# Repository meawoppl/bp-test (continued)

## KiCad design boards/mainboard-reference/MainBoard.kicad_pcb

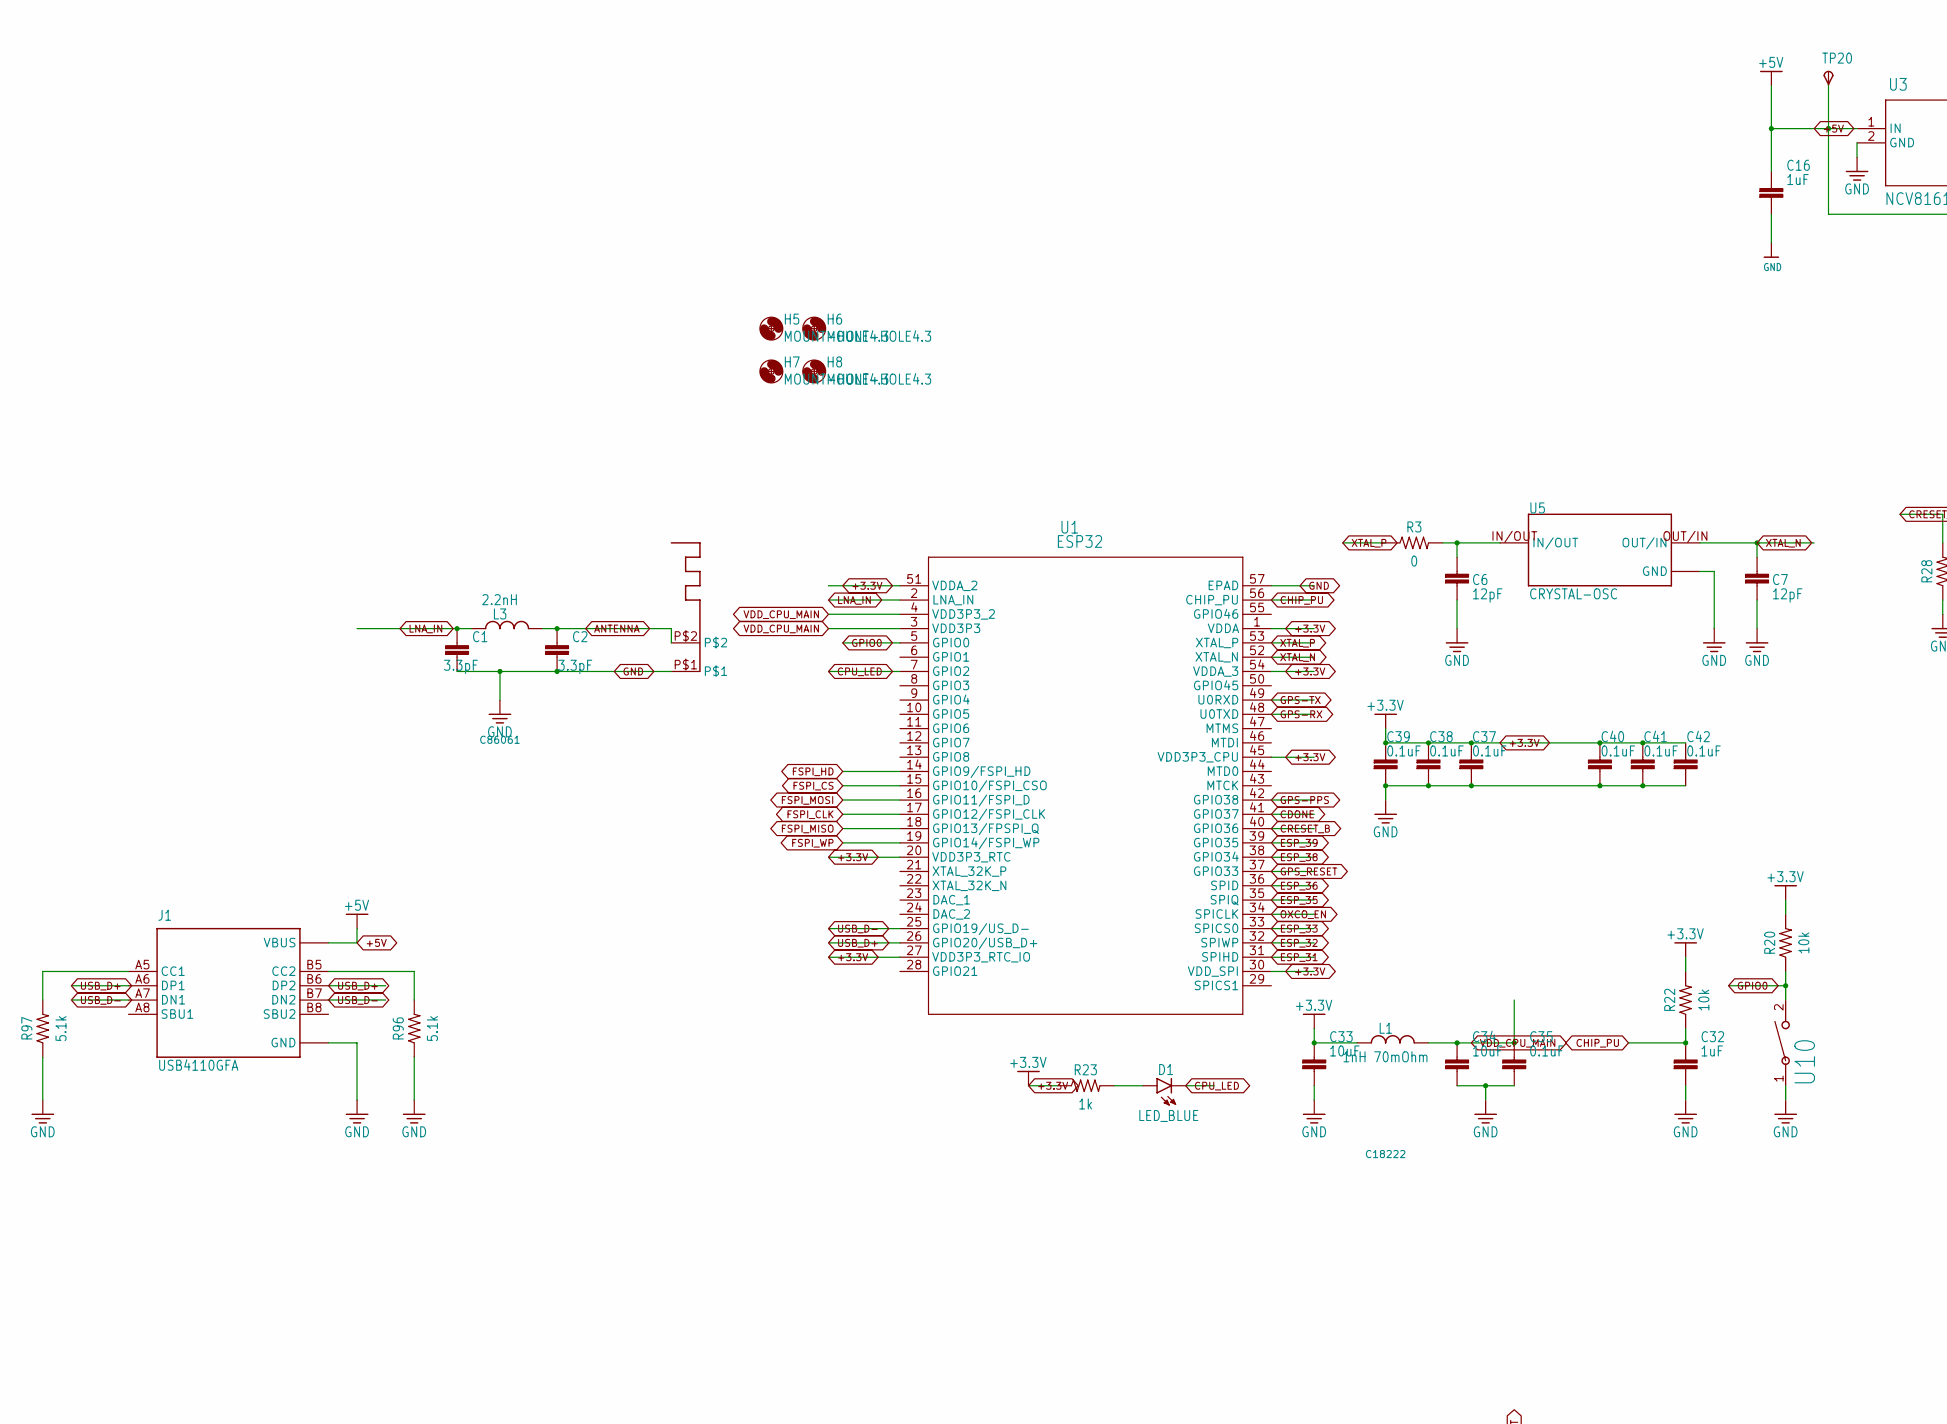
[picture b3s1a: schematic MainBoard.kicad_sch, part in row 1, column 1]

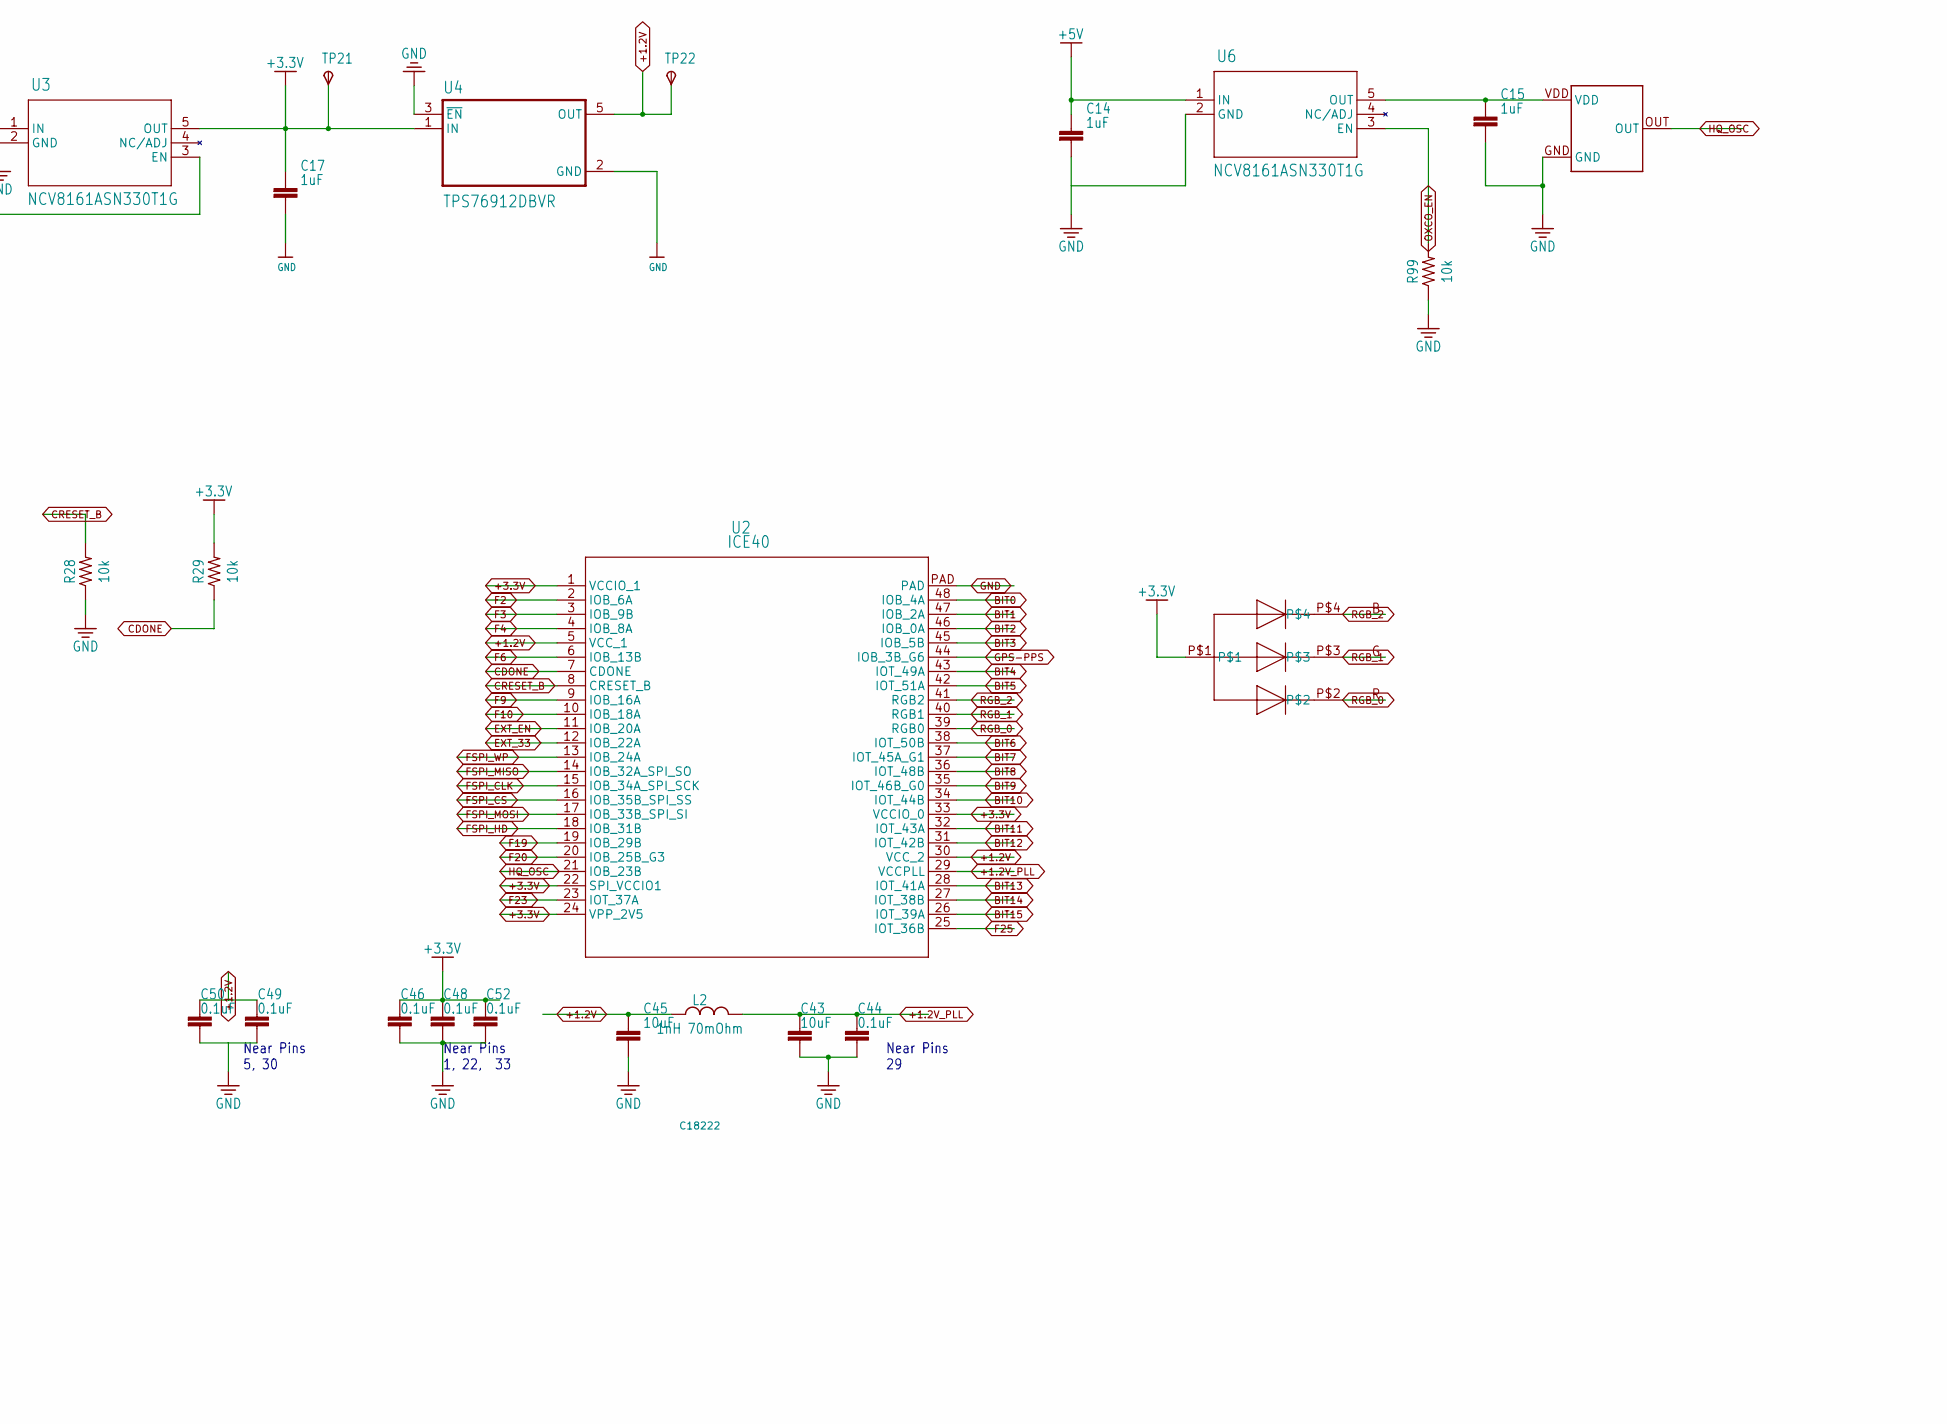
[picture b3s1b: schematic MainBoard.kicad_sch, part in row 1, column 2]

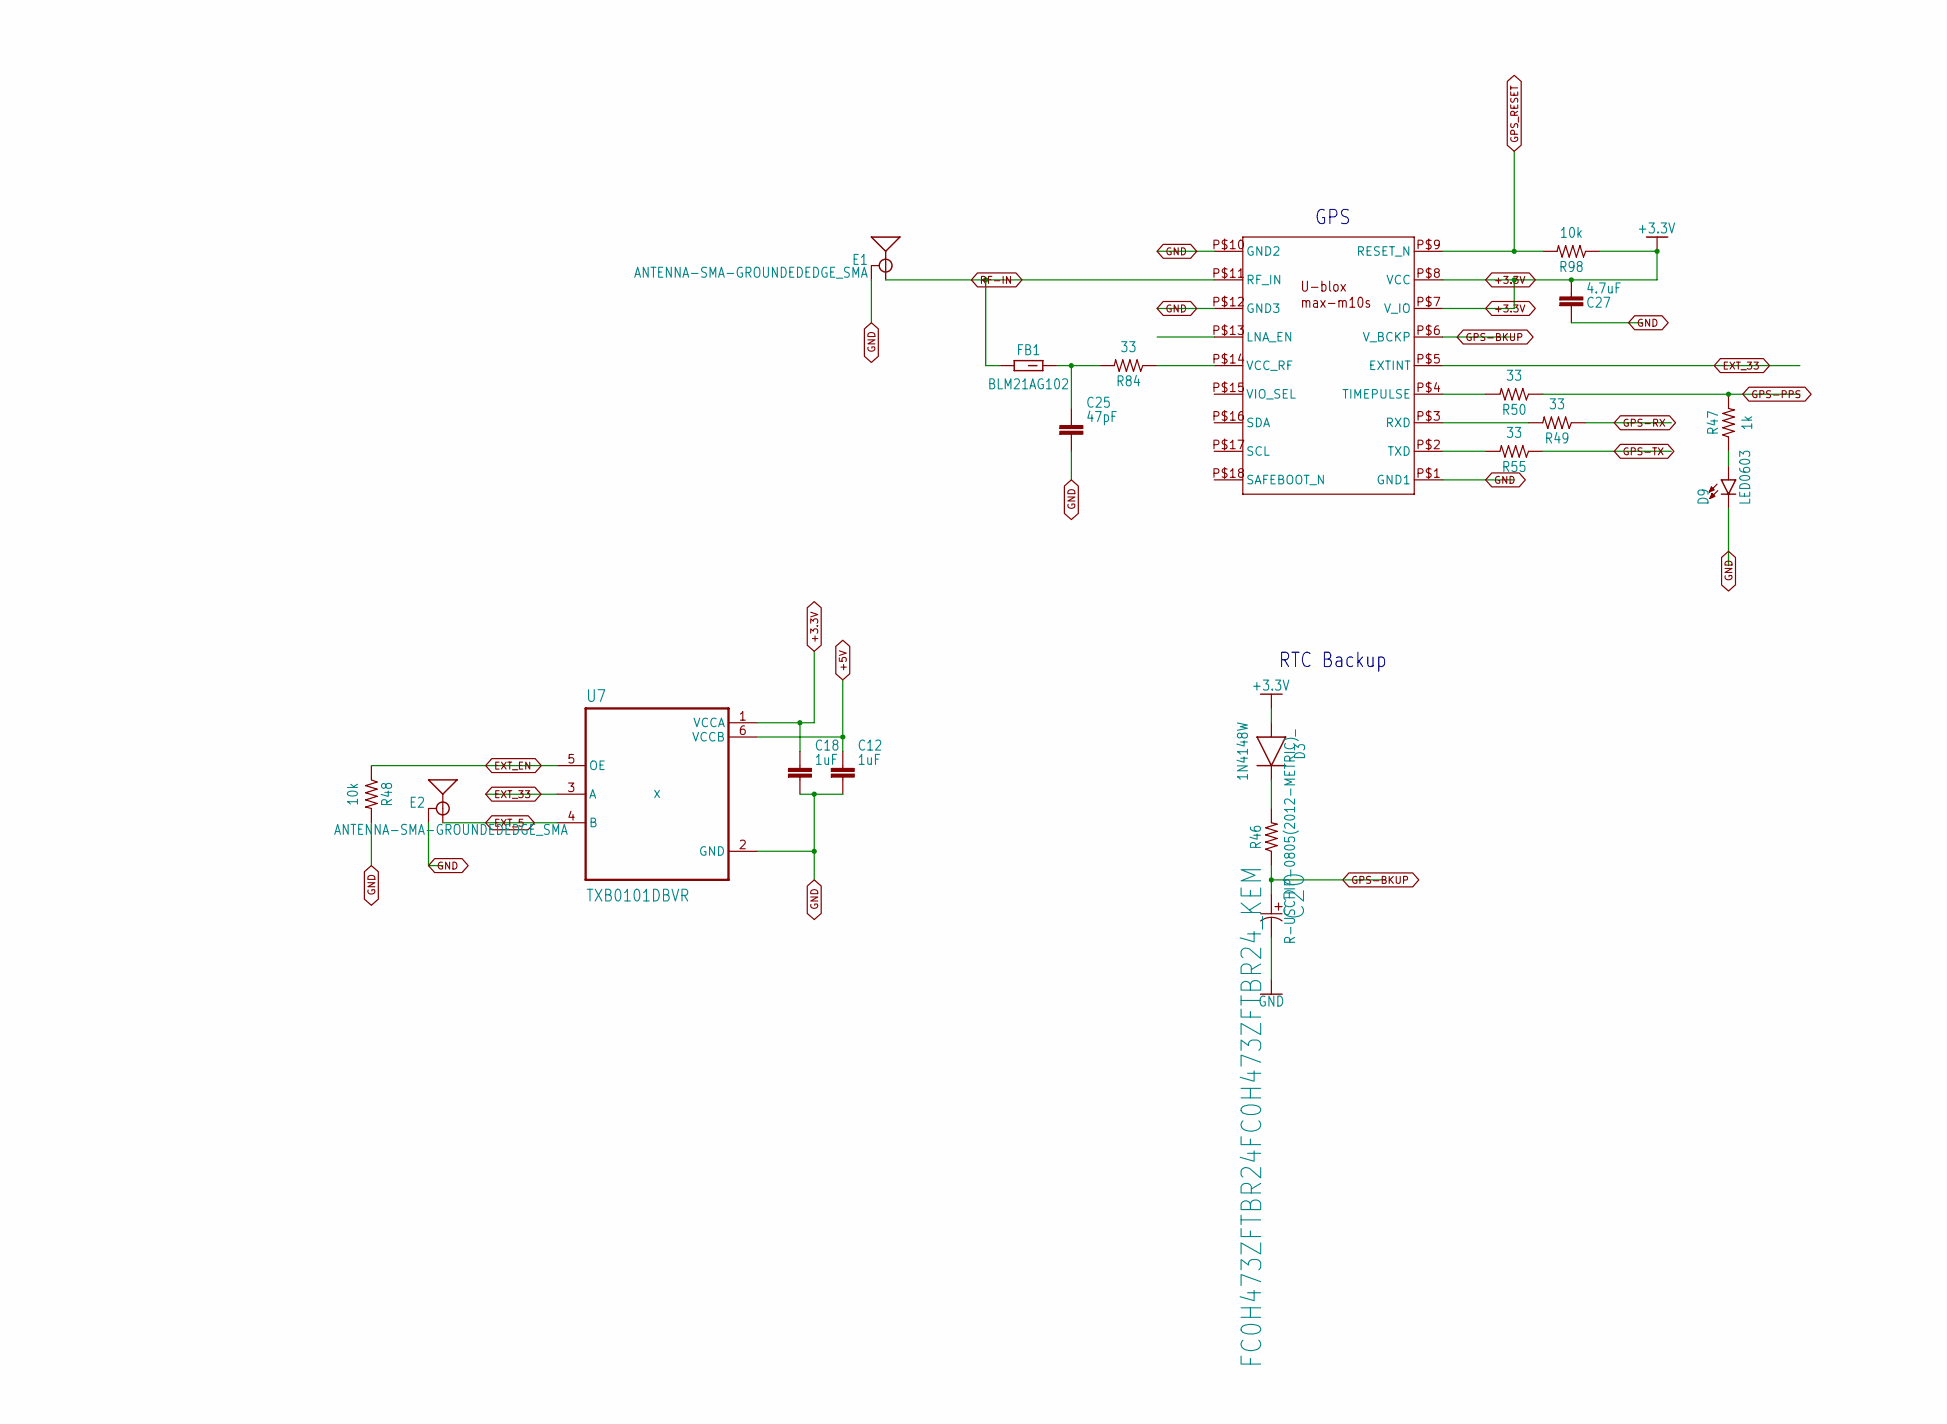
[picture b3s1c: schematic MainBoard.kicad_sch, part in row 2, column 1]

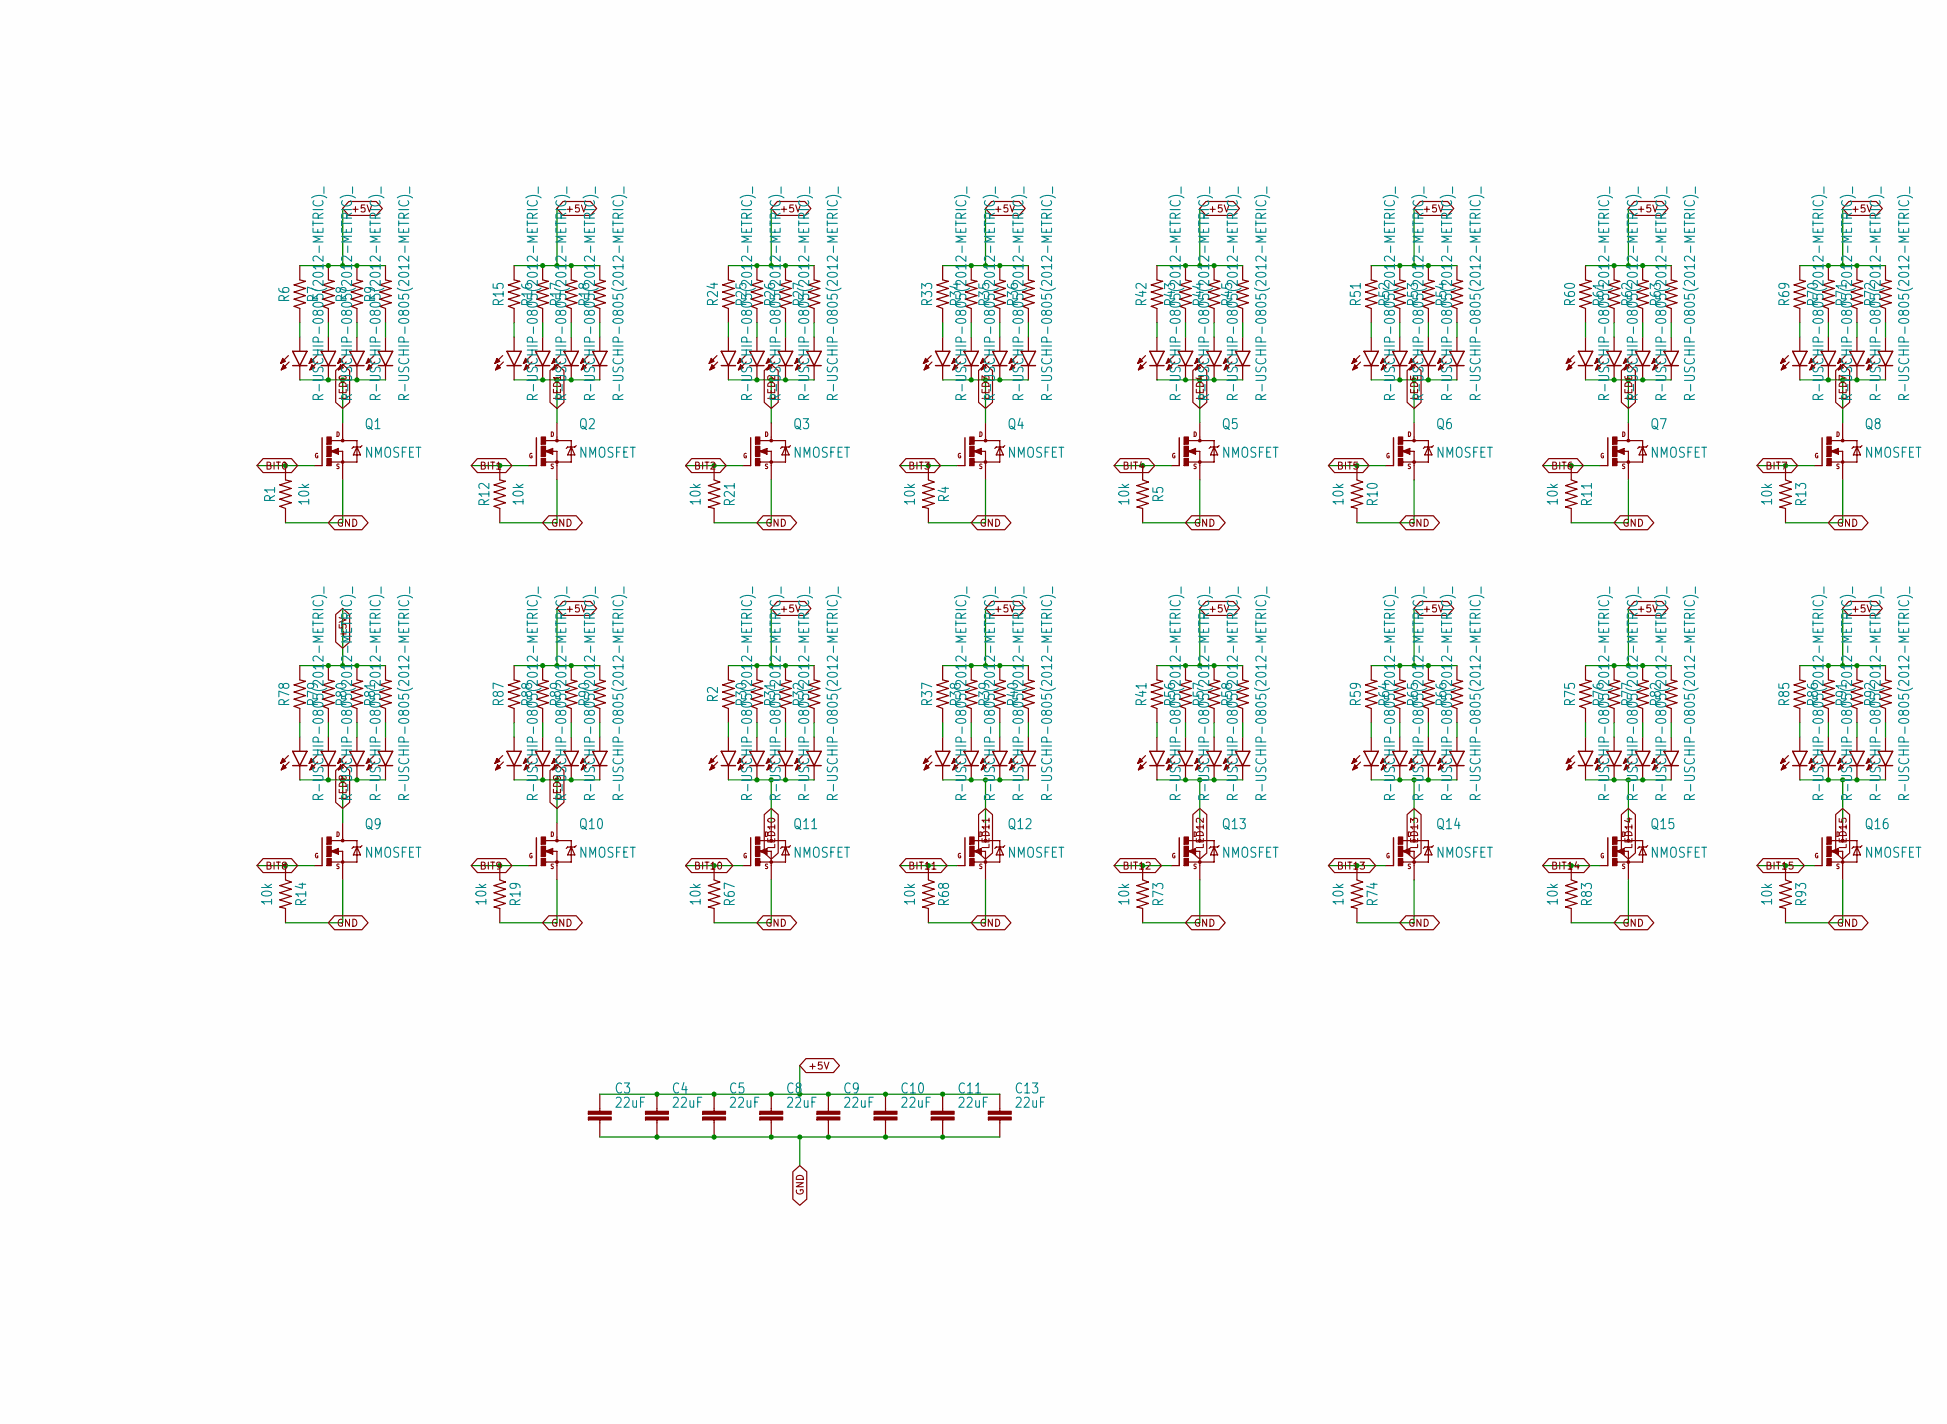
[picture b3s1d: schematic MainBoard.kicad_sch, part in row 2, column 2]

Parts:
C1, C2: 3.3pF; CAPC1005X60; LCSC_PART C76906
C3, C4, C5, C8, C9, C10, C11, C13: 22uF; CAPC3225X135; LCSC_PART C52306
C6, C7: 12pF; CAPC1005X60; LCSC_PART C26406
C12, C18, C32: 1uF; CAPC1005X60; LCSC_PART C29266
C14, C15, C16, C17: 1uF; CAPC2012X110; LCSC C28323
C20: FC0H473ZFTBR24FC0H473ZFTBR24_KEM; FC0H473ZFTBR24_KEM; MANUFACTURER_PART_NUMBER FC0H473ZFTBR24
C25: 47pF; CAPC1005X60; LCSC_PART C1671
C27: 4.7uF; CAPC1005X60; LCSC_PART C23733
C33, C34, C43, C45: 10uF; CAPC1005X60; LCSC_PART C76991
C35, C37, C38, C39, C40, C41, C42, C44, C46, C48, C49, C50, C52: 0.1uF; CAPC1005X60; LCSC_PART C1525
D1: LED_BLUE; LEDC1005X25N_FLAT-B; LCSC_PART C22355736
D2, D5, D6, D7, D8, D10, D11, D12, D13, D14, D15, D16, D17, D18, D19, D20, D21, D22, D23, D24, D25, D26, D27, D28, D29, D30, D31, D32, D33, D34, D35, D36, D37, D38, D39, D40, D41, D42, D43, D44, D45, D46, D47, D48, D49, D50, D51, D52, D53, D54, D55, D60, D61, D62, D63, D68, D69, D70, D71, D76, D77, D78, D79: LED_BLUE; LEDC3216X180N_RND-B
D3: 1N4148W; SOD3715X135; LCSC_PART C2128
D4: LED_BLUE; LEDC3216X180N_RND-B; LCSC_PART C375482
D9: LED0603; LED-0603; LCSC_PART C2286
E1, E2: ANTENNA-SMA-GROUNDEDEDGE_SMA; SMA-EDGE
FB1: BLM21AG102; BEADC2012X105N; LCSC_PART C76817
H5, H6, H7, H8: MOUNT-HOLE4.3; 4,3
J1: USB4110GFA; GCT_USB4110GFA; LCSC_PART C34260841
L1, L2: 1nH 70mOhm; INDC1006X60N; MPN BLM18KG101TN1D; LCSC_PART C18222
L3: 2.2nH; INDC1006X60N; MPN BLM18KG101TN1D; LCSC_PART C86061
Q1, Q2, Q3, Q4, Q5, Q6, Q7, Q8, Q9, Q10, Q11, Q12, Q13, Q14, Q15, Q16: NMOSFET; SOT23; LCSC_PART C478010
R1, R4, R5, R10, R11, R12, R13, R14, R19, R21, R67, R68, R73, R74, R83, R93: 10k; RESC2012X65; LCSC_PART C60490
R2, R6, R7, R8, R9, R15, R16, R17, R18, R24, R25, R26, R27, R30, R31, R32, R33, R34, R35, R36, R37, R38, R39, R40, R41, R42, R43, R44, R45, R46, R51, R52, R53, R54, R56, R57, R58, R59, R60, R61, R62, R63, R64, R65, R66, R69, R70, R71, R72, R75, R76, R77, R78, R79, R80, R81, R82, R85, R86, R87, R88, R89, R90, R91, R92: R-USCHIP-0805(2012-METRIC)_; RESC2012X65
R3: 0; RESC1005X40; LCSC_PART C17168
R20, R22, R28, R29, R48, R98, R99: 10k; RESC1005X40; LCSC_PART C60490
R23, R47: 1k; RESC1005X40; LCSC_PART C11702
R49, R50, R55, R84: 33; RESC1005X40; LCSC_PART C25105
R96, R97: 5.1k; RESC1005X40; LCSC_PART C25905
TP20, TP22: TPSB1,27; B1,27
TP21: TPSB1,27; B1,27; LCSC DNP
U1: ESP32; QFN56_ESP32-S2FH4_EXP-M; LCSC C2841141
U2: ICE40; ICE40-QFN; LCSC C2678152
U3, U6: NCV8161ASN330T1G; TSOP5_3X1P5_ONS-M; LCSC C604034
U4: TPS76912DBVR; LCSC C523754
U5: CRYSTAL-OSC; XTAL_ECS-400-10-36-CKY-TR; LCSC C555614
U7: TXB0101DBVR; SOT95P280X145-6N; LCSC C2652944
U9: RGBLED; LCSC C158099
U10: TS-1185-C-A-A-A; SW_CS1213AGF260_CRS; LCSC C561518
U11: MAX-M10S-00B
U$1: PCB-ANTENNA
U$2: ACO97

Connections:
+1.2V_PLL: C43.1, C44.1, L2.2, U2.29 (VCCPLL)
+3.3V: C17.1, C18.1, C27.1, C33.1, C37.1, C38.1, C39.1, C40.1, C41.1, C42.1, C46.1, C48.1, C52.1, D3.2 (A), L1.1, R20.2, R22.2, R23.1, R29.2, R98.1, TP21.TP, U1.1 (VDDA), U1.20 (VDD3P3_RTC), U1.27 (VDD3P3_RTC_IO), U1.30 (VDD_SPI), U1.45 (VDD3P3_CPU), U1.51 (VDDA_2), U1.54 (VDDA_3), U2.1 (VCCIO_1), U2.22 (SPI_VCCIO1), U2.24 (VPP_2V5), U2.33 (VCCIO_0), U3.5 (OUT), U4.1 (IN), U7.1 (VCCA), U9.P$1, U11.P$7 (V_IO), U11.P$8 (VCC)
+5V: C3.1, C4.1, C5.1, C8.1, C9.1, C10.1, C11.1, C12.1, C13.1, C14.1, C16.1, J1.A4/B9 (VBUS), J1.B4/A9 (VBUS), R2.2, R6.2, R7.2, R8.2, R9.2, R15.2, R16.2, R17.2, R18.2, R24.2, R25.2, R26.2, R27.2, R30.2, R31.2, R32.2, R33.2, R34.2, R35.2, R36.2, R37.2, R38.2, R39.2, R40.2, R41.2, R42.2, R43.2, R44.2, R45.2, R51.2, R52.2, R53.2, R54.2, R56.2, R57.2, R58.2, R59.2, R60.2, R61.2, R62.2, R63.2, R64.2, R65.2, R66.2, R69.2, R70.2, R71.2, R72.2, R75.2, R76.2, R77.2, R78.2, R79.2, R80.2, R81.2, R82.2, R85.2, R86.2, R87.2, R88.2, R89.2, R90.2, R91.2, R92.2, TP20.TP, U3.1 (IN), U3.3 (EN), U6.1 (IN), U7.6 (VCCB)
ANTENNA: C2.1, L3.2, U$1.P$2
BIT0: Q1.1 (G), R1.2, U2.48 (IOB_4A)
BIT1: Q2.1 (G), R12.2, U2.47 (IOB_2A)
BIT2: Q3.1 (G), R21.1, U2.46 (IOB_0A)
BIT3: Q4.1 (G), R4.1, U2.45 (IOB_5B)
BIT4: Q5.1 (G), R5.1, U2.43 (IOT_49A)
BIT5: Q6.1 (G), R10.1, U2.42 (IOT_51A)
BIT6: Q7.1 (G), R11.1, U2.38 (IOT_50B)
BIT7: Q8.1 (G), R13.1, U2.37 (IOT_45A_G1)
BIT8: Q9.1 (G), R14.1, U2.36 (IOT_48B)
BIT9: Q10.1 (G), R19.1, U2.35 (IOT_46B_G0)
BIT10: Q11.1 (G), R67.1, U2.34 (IOT_44B)
BIT11: Q12.1 (G), R68.1, U2.32 (IOT_43A)
BIT12: Q13.1 (G), R73.1, U2.31 (IOT_42B)
BIT13: Q14.1 (G), R74.1, U2.28 (IOT_41A)
BIT14: Q15.1 (G), R83.1, U2.27 (IOT_38B)
BIT15: Q16.1 (G), R93.1, U2.26 (IOT_39A)
CDONE: R29.1, U1.41 (GPIO37), U2.7 (CDONE)
CHIP_PU: C32.1, R22.1, U1.56 (CHIP_PU)
CPU_LED: D1.C, U1.7 (GPIO2)
CRESET_B: R28.2, U1.40 (GPIO36), U2.8 (CRESET_B)
ESP_31: U1.31 (SPIHD)
ESP_32: U1.32 (SPIWP)
ESP_33: U1.33 (SPICS0)
ESP_35: U1.35 (SPIQ)
ESP_36: U1.36 (SPID)
ESP_38: U1.38 (GPIO34)
ESP_39: U1.39 (GPIO35)
EXT_5: E2.SIG (SIGNAL), U7.4 (B)
EXT_33: U2.12 (IOB_22A), U7.3 (A), U11.P$5 (EXTINT)
EXT_EN: R48.1, U2.11 (IOB_20A), U7.5 (OE)
F2: U2.2 (IOB_6A)
F3: U2.3 (IOB_9B)
F4: U2.4 (IOB_8A)
F6: U2.6 (IOB_13B)
F9: U2.9 (IOB_16A)
F10: U2.10 (IOB_18A)
F19: U2.19 (IOB_29B)
F20: U2.20 (IOB_25B_G3)
F23: U2.23 (IOT_37A)
F25: U2.25 (IOT_36B)
FSPI_CLK: U1.17 (GPIO12/FSPI_CLK), U2.15 (IOB_34A_SPI_SCK)
FSPI_CS: U1.15 (GPIO10/FSPI_CSO), U2.16 (IOB_35B_SPI_SS)
FSPI_HD: U1.14 (GPIO9/FSPI_HD), U2.18 (IOB_31B)
FSPI_MISO: U1.18 (GPIO13/FPSPI_Q), U2.14 (IOB_32A_SPI_SO)
FSPI_MOSI: U1.16 (GPIO11/FSPI_D), U2.17 (IOB_33B_SPI_SI)
FSPI_WP: U1.19 (GPIO14/FSPI_WP), U2.13 (IOB_24A)
GPIO0: R20.1, U1.5 (GPIO0), U10.2
GPS-BKUP: C20.1, R46.1, U11.P$6 (V_BCKP)
GPS-PPS: R47.2, R50.1, U1.42 (GPIO38), U2.44 (IOB_3B_G6)
GPS-RX: R49.1, U1.48 (U0TXD)
GPS-TX: R55.1, U1.49 (U0RXD)
GPS_RESET: R98.2, U1.37 (GPIO33), U11.P$9 (RESET_N)
HQ_OSC: U2.21 (IOB_23B), U$2.OUT
LED0: D4.C, D5.C, D6.C, D7.C, Q1.3 (D)
LED1: D12.C, D13.C, D14.C, D15.C, Q2.3 (D)
LED2: D20.C, D21.C, D22.C, D23.C, Q3.3 (D)
LED3: D28.C, D29.C, D30.C, D31.C, Q4.3 (D)
LED4: D36.C, D37.C, D38.C, D39.C, Q5.3 (D)
LED5: D44.C, D45.C, D46.C, D47.C, Q6.3 (D)
LED6: D52.C, D53.C, D54.C, D55.C, Q7.3 (D)
LED7: D60.C, D61.C, D62.C, D63.C, Q8.3 (D)
LED8: D68.C, D69.C, D70.C, D71.C, Q9.3 (D)
LED9: D76.C, D77.C, D78.C, D79.C, Q10.3 (D)
LED10: D2.C, D8.C, D10.C, D11.C, Q11.3 (D)
LED11: D16.C, D17.C, D18.C, D19.C, Q12.3 (D)
LED12: D24.C, D25.C, D26.C, D27.C, Q13.3 (D)
LED13: D32.C, D33.C, D34.C, D35.C, Q14.3 (D)
LED14: D40.C, D41.C, D42.C, D43.C, Q15.3 (D)
LED15: D48.C, D49.C, D50.C, D51.C, Q16.3 (D)
LNA_IN: C1.1, L3.1, U1.2 (LNA_IN)
unnamed: D2.A, R2.1
unnamed: C6.1, R3.2, U5.IN/OUT
unnamed: D1.A, R23.2
unnamed: D8.A, R30.1
unnamed: D10.A, R31.1
unnamed: D11.A, R32.1
unnamed: D4.A, R6.1
unnamed: D5.A, R7.1
unnamed: D6.A, R8.1
unnamed: D7.A, R9.1
unnamed: D16.A, R37.1
unnamed: D17.A, R38.1
unnamed: D12.A, R15.1
unnamed: D13.A, R16.1
unnamed: D14.A, R17.1
unnamed: D15.A, R18.1
unnamed: D18.A, R39.1
unnamed: D19.A, R40.1
unnamed: D24.A, R41.1
unnamed: D25.A, R56.1
unnamed: D26.A, R57.1
unnamed: D20.A, R24.1
unnamed: D21.A, R25.1
unnamed: D22.A, R26.1
unnamed: D23.A, R27.1
unnamed: D27.A, R58.1
unnamed: D32.A, R59.1
unnamed: R84.1, U11.P$14 (VCC_RF)
unnamed: D28.A, R33.1
unnamed: D29.A, R34.1
unnamed: D30.A, R35.1
unnamed: D31.A, R36.1
unnamed: C25.1, FB1.2, R84.2
unnamed: D9.A, R47.1
unnamed: D3.1 (C), R46.2
unnamed: D33.A, R64.1
unnamed: D36.A, R42.1
unnamed: D37.A, R43.1
unnamed: D38.A, R44.1
unnamed: D39.A, R45.1
unnamed: R50.2, U11.P$4 (TIMEPULSE)
unnamed: R49.2, U11.P$3 (RXD)
unnamed: R55.2, U11.P$2 (TXD)
unnamed: D34.A, R65.1
unnamed: D35.A, R66.1
unnamed: D44.A, R51.1
unnamed: D45.A, R52.1
unnamed: D46.A, R53.1
unnamed: D47.A, R54.1
unnamed: D40.A, R75.1
unnamed: D41.A, R76.1
unnamed: D42.A, R77.1
unnamed: D43.A, R82.1
unnamed: J1.A5 (CC1), R97.2
unnamed: D52.A, R60.1
unnamed: D53.A, R61.1
unnamed: D54.A, R62.1
unnamed: D55.A, R63.1
unnamed: J1.B5 (CC2), R96.2
unnamed: C15.1, U6.5 (OUT), U$2.VDD
unnamed: D48.A, R85.1
unnamed: D60.A, R69.1
unnamed: D61.A, R70.1
unnamed: D62.A, R71.1
unnamed: D63.A, R72.1
unnamed: D49.A, R86.1
unnamed: D50.A, R91.1
unnamed: D51.A, R92.1
unnamed: D68.A, R78.1
unnamed: D69.A, R79.1
unnamed: D70.A, R80.1
unnamed: D71.A, R81.1
unnamed: D76.A, R87.1
unnamed: D77.A, R88.1
unnamed: D78.A, R89.1
unnamed: D79.A, R90.1
OXCO_EN: R99.2, U1.34 (SPICLK), U6.3 (EN)
RF-IN: E1.SIG (SIGNAL), FB1.1, U11.P$11 (RF_IN)
RGB_0: U2.39 (RGB0), U9.P$2
RGB_1: U2.40 (RGB1), U9.P$3
RGB_2: U2.41 (RGB2), U9.P$4
USB_D+: J1.A6 (DP1), J1.B6 (DP2), U1.26 (GPIO20/USB_D+)
USB_D-: J1.A7 (DN1), J1.B7 (DN2), U1.25 (GPIO19/US_D-)
VDD_CPU_MAIN: C34.1, C35.1, L1.2, U1.3 (VDD3P3), U1.4 (VDD3P3_2)
XTAL_N: C7.1, U1.52 (XTAL_N), U5.OUT/IN
XTAL_P: R3.1, U1.53 (XTAL_P)

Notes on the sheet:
RTC Backup
Near Pins 5, 30
Near Pins 29
GPS
Near Pins 1, 22, 33

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
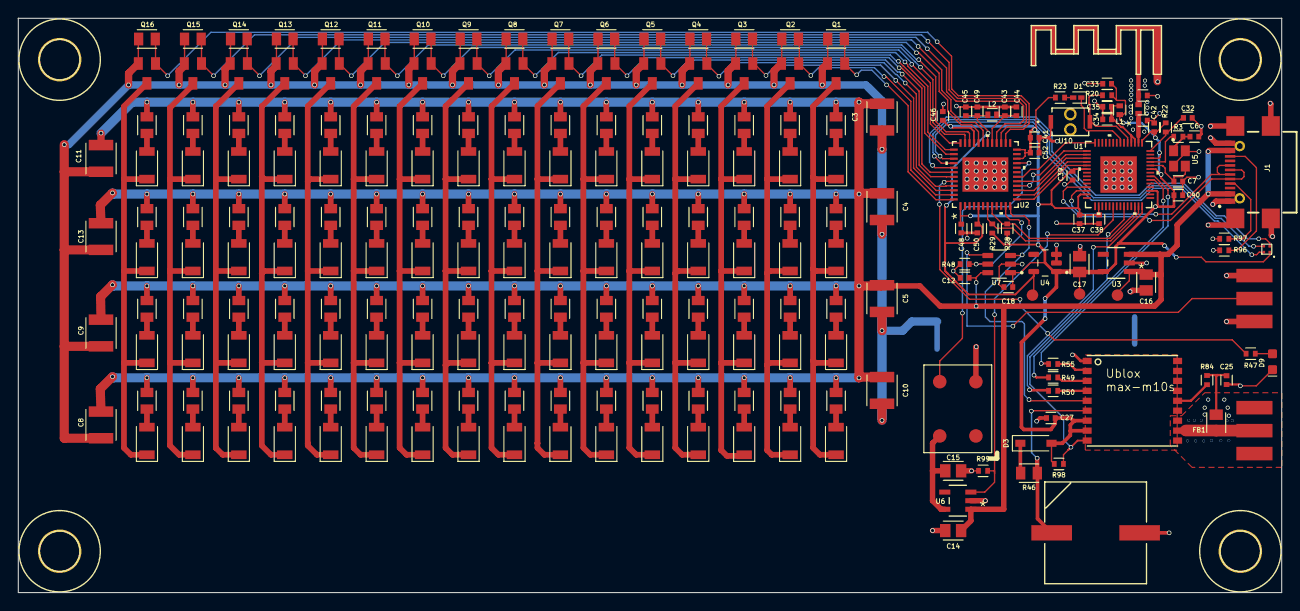
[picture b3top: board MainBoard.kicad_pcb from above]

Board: 2 copper layers, 139.7 x 63.5 mm, 245 parts (0 on the bottom side), 145 nets.
